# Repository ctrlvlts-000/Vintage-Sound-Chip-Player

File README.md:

# YM2612 Player

A desktop box where a real Yamaha YM2612 sound chip, lit behind a glass window, plays your own music files while you reach into its registers.

See [docs/DESIGN.md](docs/DESIGN.md) for the design.

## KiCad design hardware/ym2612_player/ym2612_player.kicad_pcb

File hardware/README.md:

# YM2612 player hardware (Rev B)

The Rev B board, drawn in KiCad. It follows [docs/DESIGN.md](../docs/DESIGN.md). The goal is a
**PCBWay turnkey prototype**: PCBWay makes the board, buys the parts and solders them on. Joey supplies
the YM2612 and plugs it into the socket.

**Status:** Rev B, the Rev A circuit and part positions re-routed after the Oct 30 peer review (see "Rev B changes").
Checked in KiCad 7 in the cloud: DRC 0 errors, 0 unconnected pads and 0 silkscreen warnings. ERC and a final DRC
still need running in KiCad 10. Not ordered yet: see "Still to do before ordering".

## Rev B changes (peer review, Oct 30)

Same circuit, same part positions (the case and 3D model still fit). What changed on the board:

| Review point | Rev A | Rev B |
| --- | --- | --- |
| Clearances | 0.20 mm tracks and gaps, routed right at the limit; vias 0.6 / 0.3 mm (0.15 mm ring, PCBWay's minimum) | 0.25 mm tracks and gaps; vias 0.7 / 0.3 mm (0.2 mm ring). Only the headphone amp's own 0.5 mm-pitch pins keep 0.2 mm (`HP_amp` net class and `ym2612_player.kicad_dru`) |
| Ground traces | 271 ground track pieces, 917 mm, mostly on top of the ground plane | Ground left to the planes. 20 short pieces (49 mm in all) remain where a pad needs one: chip pins onto U8's exposed pad, and pads in small pieces of plane joined to a via |
| Right angles | 66 corners at 90 degrees, 1 sharper | none in open track (43 cut into two 45 degree bends by `tools/miter.py`); the few left sit inside a pad or via |
| Silkscreen | 0.8 mm labels, 95 DRC warnings, 40 labels on a neighbouring part | 1.0 mm labels with a 0.15 mm stroke, none on a pad, part, other label or edge. 24 labels with no clear spot moved to the assembly (F.Fab) layer. Outlines trimmed where stock footprints drew them through pads (the 12 mm buttons). The Gerbers also cut silkscreen away from every pad |
| Logo | none | `[-] CTRLVLTS [+]` on the front silkscreen, above the buttons |
| Pad sizes | KiCad's standard footprints, IPC-7351B nominal | unchanged: these already include the IPC solder fillet margins |

**Just want to look?** Open [ym2612_player/ym2612_player.pdf](ym2612_player/ym2612_player.pdf). GitHub shows it in the browser.
The parts list is [ym2612_player/bom.csv](ym2612_player/bom.csv).
The board, seen from the top:

## Opening it in KiCad

1. Install KiCad (any version from 7 up) from <https://www.kicad.org/download/>.
2. Download this repository: on GitHub click the green **Code** button, then **Download ZIP**, and unzip it.
   (While this is still a pull request, pick its branch in the branch menu at the top left first.)
3. In KiCad choose **File > Open Project** and pick `hardware/ym2612_player/ym2612_player.kicad_pro`.
4. Double-click **ym2612_player.kicad_sch**. The first page has one box per page; double-click a box to go in,
   **Alt + Backspace** to come back out.

The files are saved in KiCad 7 format. Newer KiCad opens them and offers to upgrade them the first time you save.
If you'd rather keep working in your own **YM2612 player** project, copy these files into it, or ask Claude to do it
through folder access.

**Reading the drawing:** green lines are wires, drawn part to part (Rev B; Rev A used name tags only). A signal that
goes to another page ends in a name tag (label): tags with the same name are connected, even on different pages. A
small name on a wire is just that wire's name. `+5V`, `+5V_YM`, `+4V5A`, `+3V3` and `GND` are power connections. A
blue X means "not connected on purpose". A part crossed out in red is "do not fit": it has a footprint but PCBWay
leaves it off. The test points on the Controller page still connect by name, like probes.

## Pages

| Page | What's on it |
| --- | --- |
| Power | 5V from the Pico's USB-C, a ferrite-filtered 5V for the chip, and a quiet 4.5V LDO rail for the audio |
| Controller | Pimoroni Pico Plus 2 on two 20-pin sockets, boot-time pull resistors, spare-pin header, test points |
| Sound chip | YM2612 socket, two 74HCT541 buffers (3.3V to 5V) with 100 ohm resistors, clock options, window LEDs |
| Audio out | Model 1 style filter, balanced 1/4" outs, headphone amp with the dual slide volume |
| Front panel | 7 buttons (12 mm), data knob, I2C level shifter, LCD connector |

## The board

240 x 120 mm, 2 layers, rear edge at the top of the picture. Positions below are part centres, measured in mm from
the board's rear-left corner (x to the right, y towards the front). They are what the case needs.

| What | Where |
| --- | --- |
| M3 mounting holes | (4, 4), (236, 4), (4, 116), (236, 116) |
| M3 holes for the LCD standoffs | (126.5, 10.5), (219.5, 10.5), (126.5, 65.5), (219.5, 65.5) |
| Balanced 1/4" outs L / R (rear) | x 30.3 and 54.3, on the rear edge |
| Pico Plus 2 USB-C (rear) | x 104, on the rear edge |
| 3.5 mm headphone jack (front) | x 16, on the front edge |
| Volume slider plug (6-pin JST XH) | (36, 108); the slider itself sits in the case top |
| YM2612 socket / round chip window | window centre (73.6, 74), 44 mm across |
| LCD module (98 x 60 mm, on 15 mm standoffs) | from (124, 8) to (222, 68); its connector J6 just left of it, at about (120, 12) |
| 7 buttons, 12 mm | one row at y 98, from x 120 (Play) to x 222 (Write), 17 mm apart |
| Data knob (encoder) | shaft at (231, 80), below the LCD so the knob clears it |

Ground: one unbroken `GND` plane on both layers, tied together by stitching vias. The audio parts are grouped on the
left, away from USB, the bus and the LCD. (Rev A's first layout split the ground, which put the YM2612's bus over the
audio ground; see the fix register.)

## Ordering from PCBWay (turnkey)

Everything PCBWay asks for is in [ym2612_player/fab](ym2612_player/fab):

- `ym2612_player_gerbers.zip`: the board itself (copper, solder mask, silkscreen, outline, drill holes).
- `ym2612_player_bom.csv`: the parts list. Lines marked "Do not fit" are left off on purpose.
- `ym2612_player_cpl.csv`: where each part goes and which way it turns (the "placement" or "centroid" file).

Upload the zip on PCBWay's PCB Assembly page, choose Turnkey, then add the BOM and CPL when it asks. They check every
part before anything is made and email questions. Nothing is charged until you approve their quote.

## Choices made in this draft

- **Pico Plus 2 on sockets** (Digi-Key PIM724). It has chips and a connector on its underside, so it can't be soldered
  flat. PCBWay solders two 1x20 female sockets to the board (BOM line `U2-SKT`, Sullins PPTC201LFBN-RC, 8.5 mm).
  **Joey supplies the Pico and its two 1x20 male headers** (`U2`, `U2-HDR`, marked "Do not fit"), solders the headers
  and plugs it in, about 9 mm above the board (Joey, Oct 25).
- **YM2612 socket:** Mill-Max turned-pin, 24-pin, 600 mil wide. PCBWay solders the socket only.
- **Clock:** the Pico makes the 7.67 MHz clock (as the design doc proposes). There's an unfitted footprint for a
  7.670454 MHz oscillator can, so switching to exact Genesis pitch is a two-part change with no new board.
- **Buttons:** 12 mm Omron B3F-4055 switches with snap-on round caps (your choice, Oct 24).
- **Analog rail:** LP5907 4.5V low-noise regulator after a ferrite and an LC filter, damped by a 47 µF electrolytic.
- **YM2612 analog supply:** its A.VCC pin (22) has its own 10 ohm + 220 µF + 100 nF filter, so USB noise on the
  chip's 5V doesn't reach its DAC.
- **Decoupling:** every chip has its capacitors within a few mm of its supply pin.
- **Reset pull-downs:** 4.7k on /IC, A0 and A1, because of RP2350 erratum E9 (10k may not pull a released pin low).
- **Ground:** one solid plane, see above.
- **Audio filter:** 2.2k load, then a 3.39 kHz first-order low-pass (Model 1 style). See DESIGN.md 5.5.
- **Balanced outs:** hot and cold legs from OPA2350s, 100 ohm + 10 µF each, Neutrik NMJ6HCD2 jacks, with a 0 ohm
  ground-lift footprint on each sleeve.
- **Headphones:** TI TPA6132A2 headphone amp on the 4.5V rail, -6 dB gain, no output capacitors (Joey, Oct 25). The
  Pico's GP12 switches it on once the rail has settled, so power-up doesn't pop. Firmware must set GP12 high.

## Still to do before ordering

1. **Case:** Joey designs the enclosure around the positions above (Oct 25). Check heights too: the LCD glass sits
   about 27 to 30 mm up, the buttons with caps about 13 mm, the knob shaft about 20 mm.
2. **KiCad 10:** open the project in KiCad 10, run ERC and DRC there, then make the PCBWay files from that copy (see
   "Regenerating"). These files were made in KiCad 7 in the cloud.
3. **Encoder lugs:** compare the Bourns PEC11R mounting-lug spacing with the EC11 footprint (11.2 mm).
4. **Pico Plus 2 holes:** `ym2612.pretty/Pimoroni_PicoPlus2_Socketed` uses the standard Pico hole pattern
   (2.54 mm pitch, rows 17.78 mm apart), which Pimoroni keeps. A quick check with a real board and sockets is cheap.

Window LEDs are Lumimax LED3WAW (3 mm, warm white 2800K, Digi-Key); any 3 mm warm white will do. Add an order note
asking PCBWay not to trim their leads.

Not on the BOM (Joey buys these): Pico Plus 2 and headers, the YM2612, button caps, the encoder knob, the LCD module,
the volume slider and its cable.

## Regenerating

`tools/build.sh` rebuilds the schematic from `tools/design.py` (`tools/wires.py` draws the wires), checks every connection against the netlist, and
re-exports the PDF and BOM (needs KiCad installed). Once anyone edits the schematic in KiCad, the KiCad files become
the real source and the script should not be rerun.

Rev B: `tools/pcb_revb.sh` lists the steps that turned the Rev A placement into this layout (rules, Freerouting
without GND, ground vias and stitching, 45 degree corners, silkscreen, fab files).

`tools/layout.py` places the parts on the board (decoupling capacitors go to the pin named in `design.NEAR`),
`tools/route.py` routes it with Freerouting, `tools/stitch.py` adds the ground stitching vias, `tools/silk.py` moves
the part labels clear of pads and each other, and `tools/fab.sh` makes the PCBWay files. The same rule applies: once the board has been edited in KiCad, edit it there.

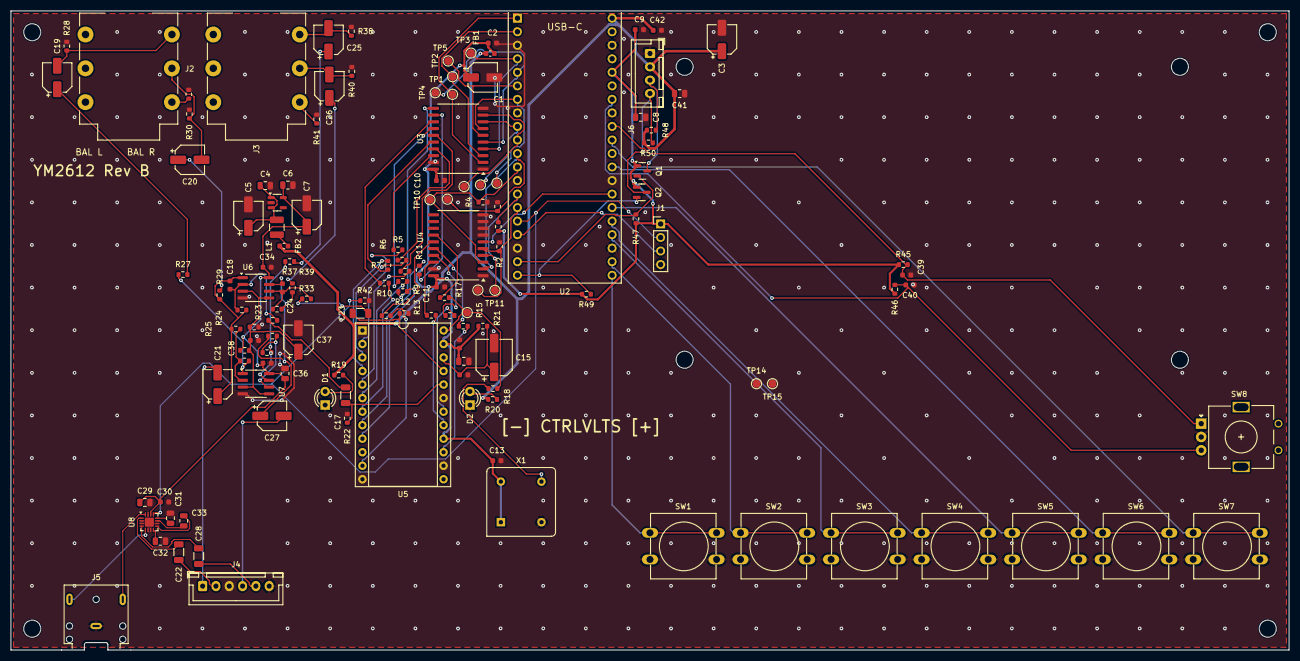
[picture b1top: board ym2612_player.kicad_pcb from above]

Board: 2 copper layers, 240.0 x 120.0 mm, 145 parts (0 on the bottom side), 100 nets.

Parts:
C1, C3, C5, C7, C37: 47uF; CP_Elec_5x5.4
C2, C9, C10, C11, C12, C13, C16, C30, C34, C35, C38, C42: 100nF; C_0603_1608Metric
C4: 22uF; C_0805_2012Metric
C6: 4.7uF; C_0805_2012Metric
C8, C14, C36, C41: 10uF; C_0805_2012Metric
C15: 220uF; CP_Elec_6.3x7.7
C17, C22, C23, C28: 1uF; C_1206_3216Metric
C18, C24: 470pF; C_0603_1608Metric
C19, C20, C21, C25, C26, C27: 10uF; CP_Elec_5x5.4
C29, C31, C32: 2.2uF; C_0805_2012Metric
C33: 1uF; C_0805_2012Metric
C39, C40: 10nF; C_0603_1608Metric
D1, D2: warm white 3 mm; LED_D3.0mm
FB1, FB2: 220R@100MHz; L_0603_1608Metric
H1, H2, H3, H4: M3; MountingHole_3.2mm_M3
H5, H6, H7, H8: M3 (LCD); MountingHole_3.2mm_M3
J1: Spare GPIO (not fitted); PinHeader_1x04_P2.54mm_Vertical
J2: 1/4" TRS balanced out L; Jack_6.35mm_Neutrik_NMJ6HCD2_Horizontal
J3: 1/4" TRS balanced out R; Jack_6.35mm_Neutrik_NMJ6HCD2_Horizontal
J4: Volume slider (dual 10k audio taper, in the case); JST_XH_B6B-XH-A_1x06_P2.50mm_Vertical
J5: 3.5 mm headphones (front); Jack_3.5mm_CUI_SJ1-3523N_Horizontal
J6: LCD (I2C backpack: GND, VCC, SDA, SCL); JST_XH_B4B-XH-A_1x04_P2.50mm_Vertical
L1: 10uH; L_1210_3225Metric
Q1, Q2: BSS138; SOT-23
R1, R25, R26, R35, R36, R43, R44, R45, R46: 10k; R_0603_1608Metric
R2, R3, R4, R42, R47, R48, R49, R50: 4.7k; R_0603_1608Metric
R5, R6, R7, R8, R9, R10, R11, R12, R13, R14, R15, R16, R27, R29, R37, R39: 100; R_0603_1608Metric
R17, R18: 33; R_0603_1608Metric
R19, R20: 430; R_0603_1608Metric
R21: 10; R_0603_1608Metric
R22, R32: 2.2k; R_0603_1608Metric
R23, R33: 47k; R_0603_1608Metric
R24, R28, R30, R34, R38, R40: 100k; R_0603_1608Metric
R31, R41: 0; R_0603_1608Metric
SW1: Play (red cap); SW_PUSH-12mm
SW2: Stop; SW_PUSH-12mm
SW3: Left; SW_PUSH-12mm
SW4: Right; SW_PUSH-12mm
SW5: Edit; SW_PUSH-12mm
SW6: Exit; SW_PUSH-12mm
SW7: Write; SW_PUSH-12mm
SW8: Data knob; RotaryEncoder_Alps_EC11E_Vertical_H20mm
TP1: D0; TestPoint_Pad_D1.5mm
TP2: D1; TestPoint_Pad_D1.5mm
TP3: D2; TestPoint_Pad_D1.5mm
TP4: D3; TestPoint_Pad_D1.5mm
TP5: D4; TestPoint_Pad_D1.5mm
TP6: D5; TestPoint_Pad_D1.5mm
TP7: D6; TestPoint_Pad_D1.5mm
TP8: D7; TestPoint_Pad_D1.5mm
TP9: A0; TestPoint_Pad_D1.5mm
TP10: A1; TestPoint_Pad_D1.5mm
TP11: WR; TestPoint_Pad_D1.5mm
TP12: IC; TestPoint_Pad_D1.5mm
TP13: YM_CLK; TestPoint_Pad_D1.5mm
TP14, TP15: GND; TestPoint_Pad_D1.5mm
U1: LP5907MFX-4.5; SOT-23-5
U2: Pimoroni Pico Plus 2; Pimoroni_PicoPlus2_Socketed
U3, U4: 74HCT541; SOIC-20W_7.5x12.8mm_P1.27mm
U5: YM2612 (socket only, chip fitted by hand); DIP-24_W15.24mm_Socket
U6, U7: OPA2350UA; SOIC-8_3.9x4.9mm_P1.27mm
U8: TPA6132A2RTER; WQFN-16-1EP_3x3mm_P0.5mm_EP1.68x1.68mm
X1: 7.670454 MHz, 5V (not fitted); Oscillator_DIP-8

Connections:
+3V3: C8.1, C9.1, J1.1, Q1.1, Q2.1, R1.1, R45.1, R46.1, R47.1, R49.1, U2.36
+4V5A: C6.1, C7.1, C29.1, C30.1, C34.1, C35.1, C36.1, R43.1, U1.5, U6.8, U7.8, U8.14
+5V: C3.1, C41.1, C42.1, FB1.1, FB2.1, J6.2, R19.1, R20.1, R48.1, R50.1, U2.40
+5V_YM: C1.1, C2.1, C10.1, C11.1, C12.1, C13.1, C14.1, FB1.2, R21.1, U3.20, U4.20, U5.16, U5.23, X1.1, X1.8
BTN_EDIT: SW5.1, U2.26
BTN_EXIT: SW6.1, U2.29
BTN_LEFT: SW3.1, U2.24
BTN_PLAY: SW1.1, U2.21
BTN_RIGHT: SW4.1, U2.25
BTN_STOP: SW2.1, U2.22
BTN_WRITE: SW7.1, U2.31
COLD_L: C18.2, C21.1, R24.2, R25.1, R29.1, U6.1
COLD_L_OUT: C20.2, J2.R, R30.1
COLD_L_R: C20.1, R29.2
COLD_R: C24.2, C27.1, R34.2, R35.1, R39.1, U6.7
COLD_R_OUT: C26.2, J3.R, R40.1
COLD_R_R: C26.1, R39.2
ENC_A: C39.1, R45.2, SW8.A, U2.32
ENC_B: C40.1, R46.2, SW8.B, U2.34
FL_IN: C17.2, R23.1
FL_SUM: C18.1, R23.2, R24.1, U6.2
FR_IN: C23.2, R33.1
FR_SUM: C24.1, R33.2, R34.1, U6.6
GND: C1.2, C2.2, C3.2, C4.2, C5.2, C6.2, C7.2, C8.2, C9.2, C10.2, C11.2, C12.2, C13.2, C14.2, C15.2, C16.2, C29.2, C30.2, C31.2, C32.2, C34.2, C35.2, C36.2, C37.2, C38.2, C39.2, C40.2, C41.2, C42.2, D1.1, D2.1, J1.4, J4.3, J4.6, J5.S, J6.1, R2.2, R3.2, R4.2, R22.2, R28.2, R30.2, R31.2, R32.2, R38.2, R40.2, R41.2, R42.2, R44.2, SW1.2, SW2.2, SW3.2, SW4.2, SW5.2, SW6.2, SW7.2, SW8.C, TP14.1, TP15.1, U1.2, U2.3, U2.8, U2.13, U2.18, U2.23, U2.28, U2.33, U2.38, U3.1, U3.10, U3.19, U4.1, U4.7, U4.8, U4.9, U4.10, U4.19, U5.1, U5.12, U5.14, U5.19, U6.4, U7.4, U8.2, U8.3, U8.6, U8.7, U8.10, U8.15, U8.17, X1.4
HOT_L: R26.2, R27.1, U7.1
HOT_L_OUT: C19.2, J2.T, R28.1
HOT_L_R: C19.1, R27.2
HOT_R: R36.2, R37.1, U7.7
HOT_R_OUT: C25.2, J3.T, R38.1
HOT_R_R: C25.1, R37.2
HPVDD: C31.1, U8.12
HPVSS: C32.1, U8.8
HP_CPN: C33.2, U8.9
HP_CPP: C33.1, U8.11
HP_EN: J1.2, R42.1, U2.16, U8.13
HP_L_IN: C22.2, U8.1
HP_R_IN: C28.2, U8.4
I2C_SCL: Q2.2, R49.2, U2.20
I2C_SDA: Q1.2, R47.2, U2.19
INV_L: R25.2, R26.1, U7.2
INV_R: R35.2, R36.1, U7.6
LCD_SCL: J6.4, Q2.3, R50.2
LCD_SDA: J6.3, Q1.3, R48.2
LED_WIN1: D1.2, R19.2
LED_WIN2: D2.2, R20.2
MCU_A0: R3.1, TP9.1, U2.11, U4.2
MCU_A1: R4.1, TP10.1, U2.12, U4.3
MCU_CLK: U2.27, U4.6
MCU_D0: TP1.1, U2.1, U3.2
MCU_D1: TP2.1, U2.2, U3.3
MCU_D2: TP3.1, U2.4, U3.4
MCU_D3: TP4.1, U2.5, U3.5
MCU_D4: TP5.1, U2.6, U3.6
MCU_D5: TP6.1, U2.7, U3.7
MCU_D6: TP7.1, U2.9, U3.8
MCU_D7: TP8.1, U2.10, U3.9
MCU_IC: R2.1, TP12.1, U2.15, U4.5
MCU_WR: R1.2, TP11.1, U2.14, U4.4
OSC_OUT: R18.1, X1.5
PHONE_L: J5.T, U8.16
PHONE_R: J5.R, U8.5
SLEEVE_L: J2.S, R31.1
SLEEVE_R: J3.S, R41.1
SPARE_GP13: J1.3, U2.17
VA_IN: C4.1, C5.1, L1.2, U1.1, U1.3
VA_RAW: FB2.2, L1.1
VOL_L_IN: C21.2, J4.1
VOL_L_W: C22.1, J4.2
VOL_R_IN: C27.2, J4.4
VOL_R_W: C28.1, J4.5
VREF: C37.1, C38.1, R43.2, R44.1, U6.3, U6.5, U7.3, U7.5
YMB_A0: R13.1, U4.18
YMB_A1: R14.1, U4.17
YMB_CLK: R17.1, U4.14
YMB_D0: R5.1, U3.18
YMB_D1: R6.1, U3.17
YMB_D2: R7.1, U3.16
YMB_D3: R8.1, U3.15
YMB_D4: R9.1, U3.14
YMB_D5: R10.1, U3.13
YMB_D6: R11.1, U3.12
YMB_D7: R12.1, U3.11
YMB_IC: R16.1, U4.15
YMB_WR: R15.1, U4.16
YM_A0: R13.2, U5.17
YM_A1: R14.2, U5.18
YM_AVCC: C15.1, C16.1, R21.2, U5.22
YM_CLK: R17.2, R18.2, TP13.1, U5.24
YM_D0: R5.2, U5.2
YM_D1: R6.2, U5.3
YM_D2: R7.2, U5.4
YM_D3: R8.2, U5.5
YM_D4: R9.2, U5.6
YM_D5: R10.2, U5.7
YM_D6: R11.2, U5.8
YM_D7: R12.2, U5.9
YM_IC: R16.2, U5.11
YM_MOL: C17.1, R22.1, U5.20
YM_MOR: C23.1, R32.1, U5.21
YM_WR: R15.2, U5.15

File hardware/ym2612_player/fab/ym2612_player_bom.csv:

Designator,Qty,Value,Manufacturer,Manufacturer Part Number,Description,Package / Footprint,Type,Fit
"C1,C3,C5,C7,C37",5,47uF,Any,generic,"electrolytic, 16V",CP_Elec_5x5.4,SMD,Fit
"C2,C9,C10,C11,C12,C13,C16,C30,C34,C35,C38,C42",12,100nF,Any,generic,"X7R, 16V",C_0603_1608Metric,SMD,Fit
C4,1,22uF,Any,generic,"X5R, 10V, 0805",C_0805_2012Metric,SMD,Fit
C6,1,4.7uF,Any,generic,"X5R, 10V, 0805",C_0805_2012Metric,SMD,Fit
"C8,C36,C41",3,10uF,Any,generic,"X5R, 10V, 0805",C_0805_2012Metric,SMD,Fit
C14,1,10uF,Any,generic,"X5R, 16V, 0805",C_0805_2012Metric,SMD,Fit
C15,1,220uF,Any,generic,"electrolytic, 16V",CP_Elec_6.3x7.7,SMD,Fit
"C17,C23",2,1uF,Any,generic,"X7R, 50V, 1206",C_1206_3216Metric,SMD,Fit
"C18,C24",2,470pF,Any,generic,"C0G, 50V",C_0603_1608Metric,SMD,Fit
"C19,C20,C25,C26",4,10uF,Any,generic,"electrolytic, 16V, low-leakage",CP_Elec_5x5.4,SMD,Fit
"C21,C27",2,10uF,Any,generic,"electrolytic, 16V",CP_Elec_5x5.4,SMD,Fit
"C22,C28",2,1uF,Any,generic,"X7R, 25V, 1206",C_1206_3216Metric,SMD,Fit
"C29,C31,C32",3,2.2uF,Any,generic,"X5R, 10V, 0805",C_0805_2012Metric,SMD,Fit
C33,1,1uF,Any,generic,"X5R, 10V, 0805 (charge-pump flying cap)",C_0805_2012Metric,SMD,Fit
"C39,C40",2,10nF,Any,generic,"X7R, 16V",C_0603_1608Metric,SMD,Fit
"D1,D2",2,warm white 3 mm,Lumimax,LED3WAW,"3 mm through-hole LED, warm white 2800K, 3.2V. Any 3 mm warm white will do. Order note for PCBWay: do not trim the leads, Joey bends them to aim the light",LED_D3.0mm,THT,Fit
"FB1,FB2",2,220R@100MHz,Murata,BLM18PG221SN1D,"ferrite bead, 0603, 1A+",L_0603_1608Metric,SMD,Fit
J1,0,Spare GPIO (not fitted),Any,generic,,PinHeader_1x04_P2.54mm_Vertical,THT,Do not fit
"J2,J3",2,"1/4"" TRS balanced out L / 1/4"" TRS balanced out R",Neutrik,NMJ6HCD2,"Neutrik 1/4in stereo jack, horizontal PCB. The footprint's SN pad is left unconnected.",Jack_6.35mm_Neutrik_NMJ6HCD2_Horizontal,THT,Fit
J4,1,"Volume slider (dual 10k audio taper, in the case)",JST,B6B-XH-A(LF)(SN),"JST XH 6-pin header. Wire a dual 10k audio-taper slide pot: L top/wiper/bottom on 1-3, R on 4-6.",JST_XH_B6B-XH-A_1x06_P2.50mm_Vertical,THT,Fit
J5,1,3.5 mm headphones (front),CUI Devices / Same Sky,SJ1-3523N,"CUI 3.5 mm stereo jack, horizontal",Jack_3.5mm_CUI_SJ1-3523N_Horizontal,THT,Fit
J6,1,"LCD (I2C backpack: GND, VCC, SDA, SCL)",JST,B4B-XH-A(LF)(SN),JST XH 4-pin header,JST_XH_B4B-XH-A_1x04_P2.50mm_Vertical,THT,Fit
L1,1,10uH,Murata,LQH32CN100K53L,"10uH, 1210, 300mA+",L_1210_3225Metric,SMD,Fit
"Q1,Q2",2,BSS138,onsemi,BSS138,"N-MOSFET, SOT-23",SOT-23,SMD,Fit
"R1,R25,R26,R35,R36,R43,R44,R45,R46",9,10k,Any,generic,"1%, 0603",R_0603_1608Metric,SMD,Fit
"R2,R3,R4,R42,R47,R48,R49,R50",8,4.7k,Any,generic,"1%, 0603",R_0603_1608Metric,SMD,Fit
"R5,R6,R7,R8,R9,R10,R11,R12,R13,R14,R15,R16,R27,R29,R37,R39",16,100,Any,generic,"1%, 0603",R_0603_1608Metric,SMD,Fit
R17,1,33,Any,generic,"1%, 0603",R_0603_1608Metric,SMD,Fit
R18,0,33,Any,generic,"1%, 0603",R_0603_1608Metric,SMD,Do not fit
"R19,R20",2,430,Any,generic,"1%, 0603",R_0603_1608Metric,SMD,Fit
R21,1,10,Any,generic,"1%, 0603 (A.VCC filter)",R_0603_1608Metric,SMD,Fit
"R22,R32",2,2.2k,Any,generic,"1%, 0603",R_0603_1608Metric,SMD,Fit
"R23,R33",2,47k,Any,generic,"1%, 0603",R_0603_1608Metric,SMD,Fit
"R24,R28,R30,R34,R38,R40",6,100k,Any,generic,"1%, 0603",R_0603_1608Metric,SMD,Fit
"R31,R41",2,0,Any,generic,"0 ohm, 0603 (ground lift option)",R_0603_1608Metric,SMD,Fit
"SW1,SW2,SW3,SW4,SW5,SW6,SW7",7,Play (red cap) / Stop / Left / Right / Edit / Exit / Write,Omron,B3F-4055,"Omron 12 mm tactile switch, 7.3 mm tall, with a B32-series snap-on round cap",SW_PUSH-12mm,THT,Fit
SW8,1,Data knob,Bourns,PEC11R-4215F-N0024,"Bourns 24-step encoder, no push switch, 15 mm shaft (EC11 footprint)",RotaryEncoder_Alps_EC11E_Vertical_H20mm,THT,Fit
U1,1,LP5907MFX-4.5,Texas Instruments,LP5907MFX-4.5/NOPB,"low-noise LDO, 4.5V, 250mA",SOT-23-5,SMD,Fit
U2,0,Pimoroni Pico Plus 2,Pimoroni,PIM724,Joey supplies the Pico Plus 2 and solders 2x 20-pin male headers to it; it plugs into sockets U2-SKT,Pimoroni_PicoPlus2_Socketed,THT,Do not fit
"U3,U4",2,74HCT541,Nexperia,"74HCT541D,653","octal buffer, HCT, SOIC-20",SOIC-20W_7.5x12.8mm_P1.27mm,SMD,Fit
U5,1,"YM2612 (socket only, chip fitted by hand)",Mill-Max,110-43-624-41-001000,Mill-Max 24-pin 600 mil turned-pin DIP socket. PCBWay fits the socket only.,DIP-24_W15.24mm_Socket,THT,Fit
"U6,U7",2,OPA2350UA,Texas Instruments,OPA2350UA,"dual rail-to-rail op-amp, 2.7-5.5V",SOIC-8_3.9x4.9mm_P1.27mm,SMD,Fit
U8,1,TPA6132A2RTER,Texas Instruments,TPA6132A2RTER,"TI DirectPath stereo headphone amp, 2.3-5.5V, WQFN-16 3x3 mm (RTE)",WQFN-16-1EP_3x3mm_P0.5mm_EP1.68x1.68mm,SMD,Fit
X1,0,"7.670454 MHz, 5V (not fitted)",Any,generic,"half-size DIP-8 oscillator can, 5V CMOS, 7.670454 MHz",Oscillator_DIP-8,THT,Do not fit
U2-SKT,2,"1x20 female socket, 2.54 mm",Sullins,PPTC201LFBN-RC,"Soldered to the board in U2's two rows of holes, 8.5 mm tall",1x20 P2.54mm vertical,THT,Fit
U2-HDR,0,"1x20 male header, 2.54 mm",Any,generic,Joey supplies and solders these to the Pico Plus 2 (U2) so it plugs into U2-SKT,1x20 P2.54mm vertical,THT,Do not fit

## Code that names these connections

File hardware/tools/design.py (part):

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flag(pw, 137.16, 55.88, "+5V_YM")
cap(pw, "47uF", 50.8, 71.12, "+5V", polar=True, near=("U2", "40"))

pw.add("Device:FerriteBead", "FB", "220R@100MHz", 71.12, 104.14, {"1": "+5V", "2": "VA_RAW"}, rot=90,
       fields=f(FP_FB, "BLM18PG221SN1D", "ferrite bead, 0603, 1A+"))
pw.add("Device:L", "L", "10uH", 109.22, 104.14, {"1": "VA_RAW", "2": "VA_IN"}, rot=90,
       fields=f("Inductor_SMD:L_1210_3225Metric", "LQH32CN100K53L", "10uH, 1210, 300mA+"))
cap(pw, "22uF", 137.16, 114.3, "VA_IN", fp=FP_C0805, spec="X5R, 10V, 0805", near=("U1", "1"))
# The electrolytic's own resistance damps the 10uH / 22uF resonance (it peaked +6 dB at 15 kHz without it).
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    sc.add(R, "R", "100", 114.3 + i * 10.16, 127, {"1": f"YMB_{s_}", "2": f"YM_{s_}"}, rot=180, fields=f(FP_R, spec="1%, 0603"))
# Clock: fit R17 for the Pico's clock (default) or R18 + X1 for an oscillator can. Never both.
sc.add(R, "R", "33", 154.94, 127, {"1": "YMB_CLK", "2": "YM_CLK"}, rot=180, fields=f(FP_R, spec="1%, 0603"))
# R18 lies with its YM_CLK end facing right, into open space for the net's label.
sc.add(R, "R", "33", 162.56, 175.26, {"1": "OSC_OUT", "2": "YM_CLK"}, rot=90, fields=f(FP_R, spec="1%, 0603"), dnp=True)
sc.add("Oscillator:CXO_DIP8", "X", "7.670454 MHz, 5V (not fitted)", 139.7, 175.26,
       {"1": "+5V_YM", "4": "GND", "5": "OSC_OUT", "8": "+5V_YM"},
       fields=f("Oscillator:Oscillator_DIP-8", "", "half-size DIP-8 oscillator can, 5V CMOS, 7.670454 MHz"), dnp=True)
sc.label_at = {"YM_CLK": "R18"}
# The data bus fans out from the buffer to the resistors and back in to the chip as two neat staircases.
sc.paths = {}
for i in range(8):
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cap(au, "1uF", 525.78, 251.46, "HP_CPP", "HP_CPN", fp=FP_C0805, spec="X5R, 10V, 0805 (charge-pump flying cap)", near=("U8", "11"))
res(au, "4.7k", 538.48, 251.46, "HP_EN", "GND")
flag(au, 518.16, 187.96, "HPVDD")
au.label_at = {"HP_EN": "R42"}
flag(au, 520.7, 240.03, "HPVSS")
if not SLIDER_ON_BOARD:
    au.add("Connector_Generic:Conn_01x06", "J", "Volume slider (dual 10k audio taper, in the case)", 444.5, 215.9,
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    fp.add("Switch:SW_Push", "SW", name, 45.72 + i * 22.86, 83.82, {"1": net, "2": "GND"}, rot=270,
           fields=f("Button_Switch_THT:SW_PUSH-12mm", "B3F-4055",
                    "Omron 12 mm tactile switch, 7.3 mm tall, with a B32-series snap-on round cap"))
fp.add("Device:RotaryEncoder", "SW", "Data knob", 66.04, 147.32, {"A": "ENC_A", "B": "ENC_B", "C": "GND"}, rot=90,
       fields=f("Rotary_Encoder:RotaryEncoder_Alps_EC11E_Vertical_H20mm", "PEC11R-4215F-N0024",
                "Bourns 24-step encoder, no push switch, 15 mm shaft (EC11 footprint)"), stagger=True)
res(fp, "10k", 114.3, 139.7, "+3V3", "ENC_A")
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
